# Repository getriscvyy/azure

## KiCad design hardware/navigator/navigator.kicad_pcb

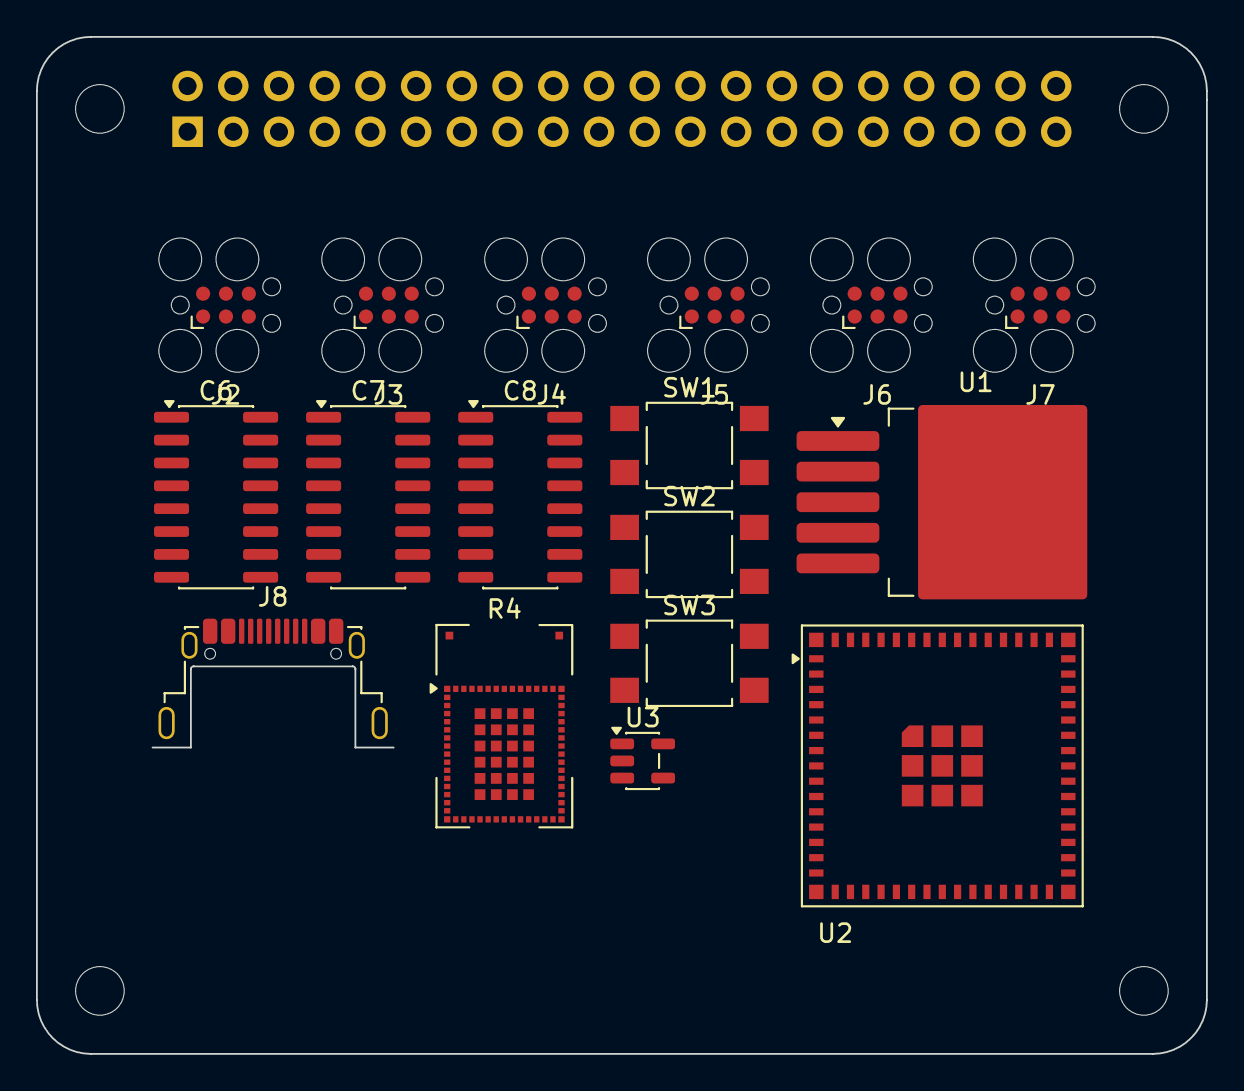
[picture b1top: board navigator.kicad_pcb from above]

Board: 2 copper layers, 65.0 x 56.5 mm, 22 parts (1 on the bottom side), 17 nets, no tracks yet.

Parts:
C6, C7: 1uF; SOIC-16_3.9x9.9mm_P1.27mm
C8: 0.1uF; SOIC-16_3.9x9.9mm_P1.27mm
J1: GPIO; PinSocket_2x20_P2.54mm_Vertical
J2, J3, J4, J5, J6, J7: BLDC-1; Tag-Connect_TC2030-IDC-FP_2x03_P1.27mm_Vertical
J8: USB_C_Receptacle_USB2.0_16P; USB_C_Receptacle_Amphenol_12401948E412A
MH1, MH2, MH3, MH4: MountingHole_2.7mm_M2.5
R4: 47k; ST-SiP-LGA-86-11x7.3mm
SW1, SW2, SW3: SW_SPST; SW_SPST_TL3305A
U1: LM2576HVS-5; TO-263-5_TabPin3
U2: ESP32-S3-MINI-1U; ESP32-S2-MINI-1U
U3: AP2112K-3.3; SOT-23-5

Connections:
+3V3: C6.1, U2.3 (3V3), U3.5 (VOUT)
+5V: J1.2, J1.4, U1.4 (FB), U3.1 (VIN), U3.3 (EN)
/BLDC_1: J2.3, U2.5 (IO1)
/BLDC_2: J3.3, U2.6 (IO2)
/BLDC_3: J4.3, U2.7 (IO3)
/BLDC_4: J5.3, U2.8 (IO4)
/BLDC_5: J6.3, U2.9 (IO5)
/BLDC_6: J7.3, U2.10 (IO6)
/BMS: R4.1, U2.11 (IO7)
/BOOT: C8.1, SW3.2 (B), U2.4 (IO0)
/D+: J8.A6 (D+), J8.B6 (D+), U2.24 (USB_D+)
/D-: J8.A7 (D-), J8.B7 (D-), U2.23 (USB_D-)
/GPIO14/TXD0: J1.8, U2.40 (RXD0)
/GPIO15/RXD0: J1.10, U2.39 (TXD0)
/RST: C7.1, SW2.2 (B), U2.45 (EN)
/VBAT: R4.2, SW1.2 (B), U1.1 (VIN)
GND: C6.2, C7.2, C8.2, J1.6, J1.9, J1.14, J1.20, J1.25, J1.30, J1.34, J1.39, J2.1, J3.1, J4.1, J5.1, J6.1, J7.1, J8.A1 (GND), J8.A12 (GND), J8.B1 (GND), J8.B12 (GND), J8.SH (SHIELD), SW2.1 (A), SW3.1 (A), U1.3 (GND), U1.5 (~ON/OFF), U2.1 (GND), U2.2 (GND), U2.42 (GND), U2.43 (GND), U2.46 (GND), U2.47 (GND), U2.48 (GND), U2.49 (GND), U2.50 (GND), U2.51 (GND), U2.52 (GND), U2.53 (GND), U2.54 (GND), U2.55 (GND), U2.56 (GND), U2.57 (GND), U2.58 (GND), U2.59 (GND), U2.60 (GND), U2.61 (GND), U2.62 (GND), U2.63 (GND), U2.64 (GND), U2.65 (GND), U3.2 (GND)
